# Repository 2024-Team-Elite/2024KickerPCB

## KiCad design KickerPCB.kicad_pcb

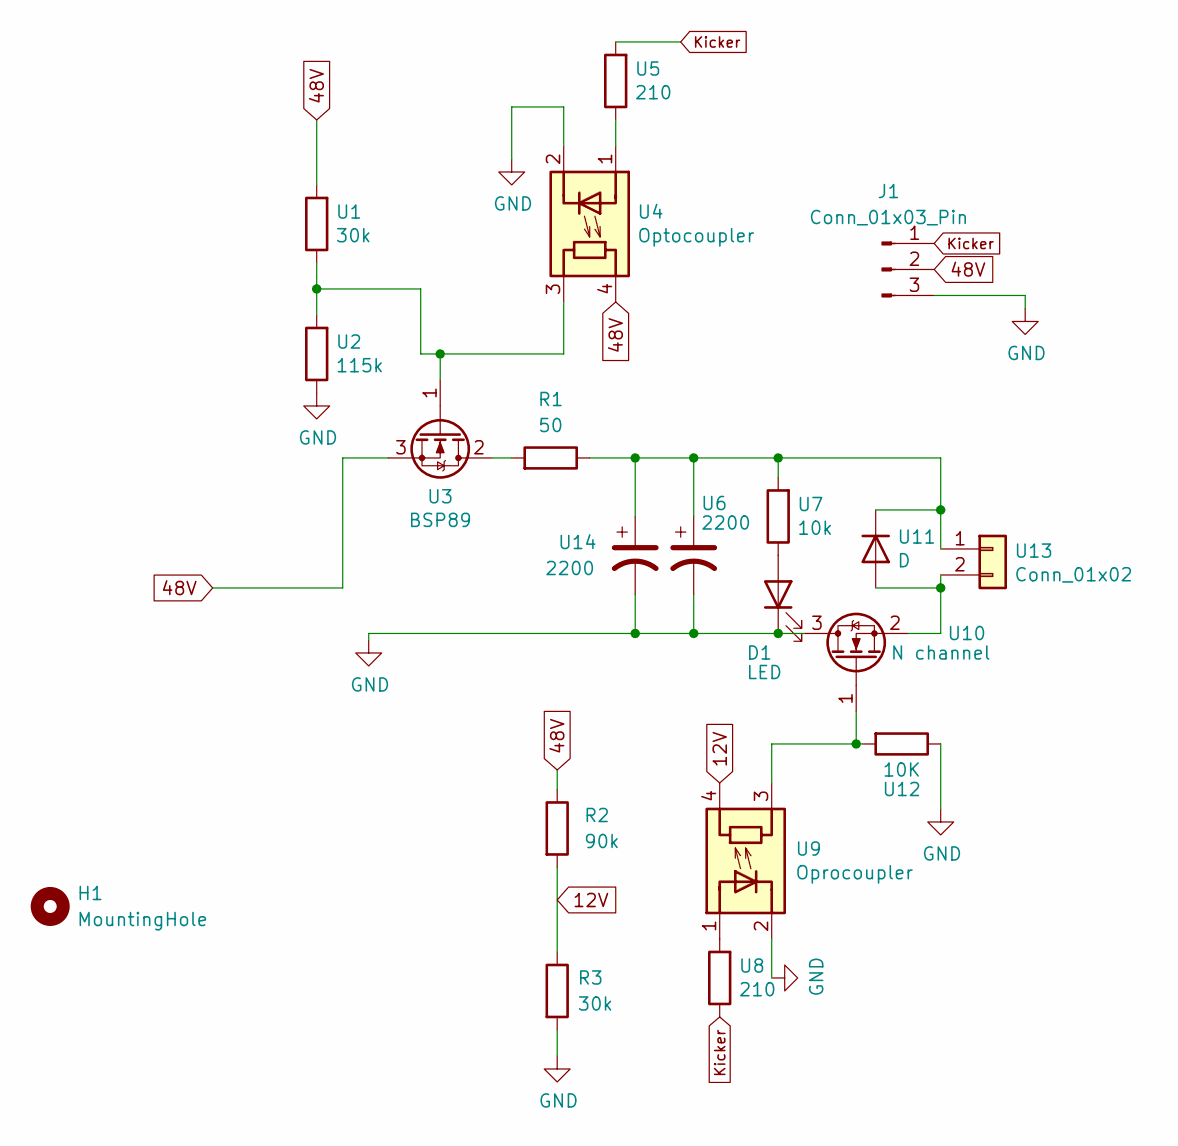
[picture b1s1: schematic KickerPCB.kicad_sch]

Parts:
D1: LED; LED_0805_2012Metric_Pad1.15x1.40mm_HandSolder
H1: MountingHole; MountingHole_3.2mm_M3_DIN965_Pad
J1: Conn_01x03_Pin; PinHeader_1x03_P2.54mm_Vertical
R1: 50; TO-220-2_Vertical
R2: 90k; R_0805_2012Metric_Pad1.20x1.40mm_HandSolder
R3: 30k; R_0805_2012Metric_Pad1.20x1.40mm_HandSolder
U1: 30k; R_0805_2012Metric_Pad1.20x1.40mm_HandSolder
U2: 115k; R_0805_2012Metric_Pad1.20x1.40mm_HandSolder
U3: BSP89; TO-220-3_Vertical
U4: Optocoupler; DIP-4_W7.62mm
U5, U8: 210; R_0805_2012Metric_Pad1.20x1.40mm_HandSolder
U6, U14: 2200; CP_Radial_D18.0mm_P7.50mm
U7: 10k; R_0805_2012Metric_Pad1.20x1.40mm_HandSolder
U9: Oprocoupler; DIP-4_W7.62mm
U10: N channel; TO-220-3_Vertical
U11: D; D_5W_P12.70mm_Horizontal
U12: 10K; R_0805_2012Metric_Pad1.20x1.40mm_HandSolder
U13: Conn_01x02; Pads_1x02

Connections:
12V: R2.2, R3.1, U9.4 (R)
48V: J1.2, R2.1, U1.2, U3.3 (S), U4.4 (R)
GND: D1.1 (K), J1.3, R3.2, U2.1, U4.2 (K), U6.2, U9.2 (K), U10.3 (D), U12.1, U14.2
Kicker: J1.1, U5.2, U8.1
unnamed: D1.2 (A), U7.1
unnamed: R1.2, U3.2 (D)
unnamed: U1.1, U2.2, U3.1 (G), U4.3 (R)
unnamed: U4.1 (A), U5.1
unnamed: U8.2, U9.1 (A)
unnamed: U9.3 (R), U10.1 (G), U12.2
unnamed: U10.2 (S), U11.2 (A), U13.2
unnamed: R1.1, U6.1, U7.2, U11.1 (K), U13.1, U14.1

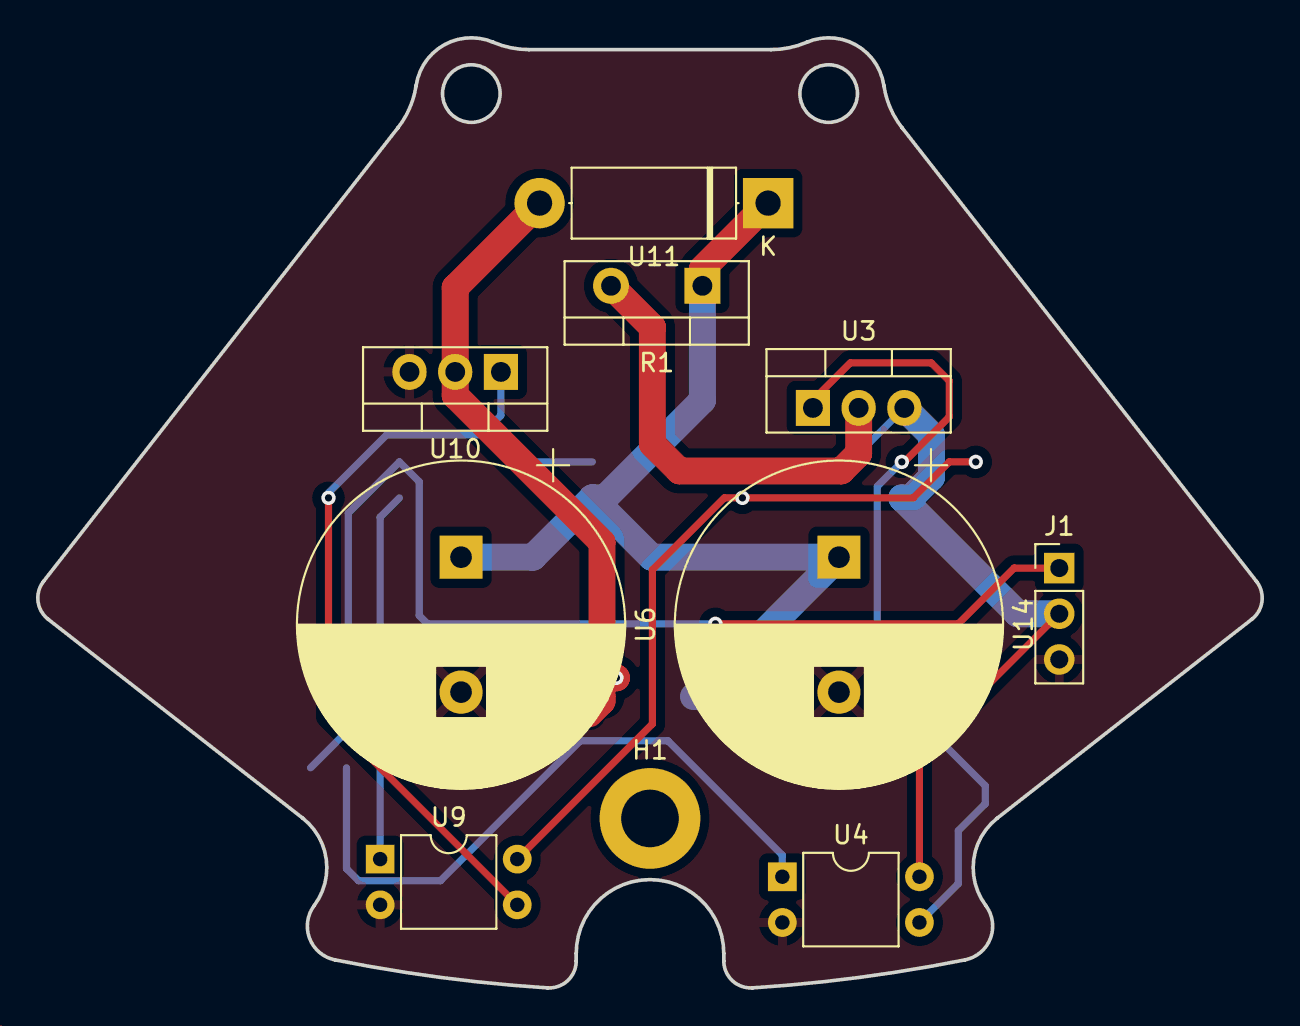
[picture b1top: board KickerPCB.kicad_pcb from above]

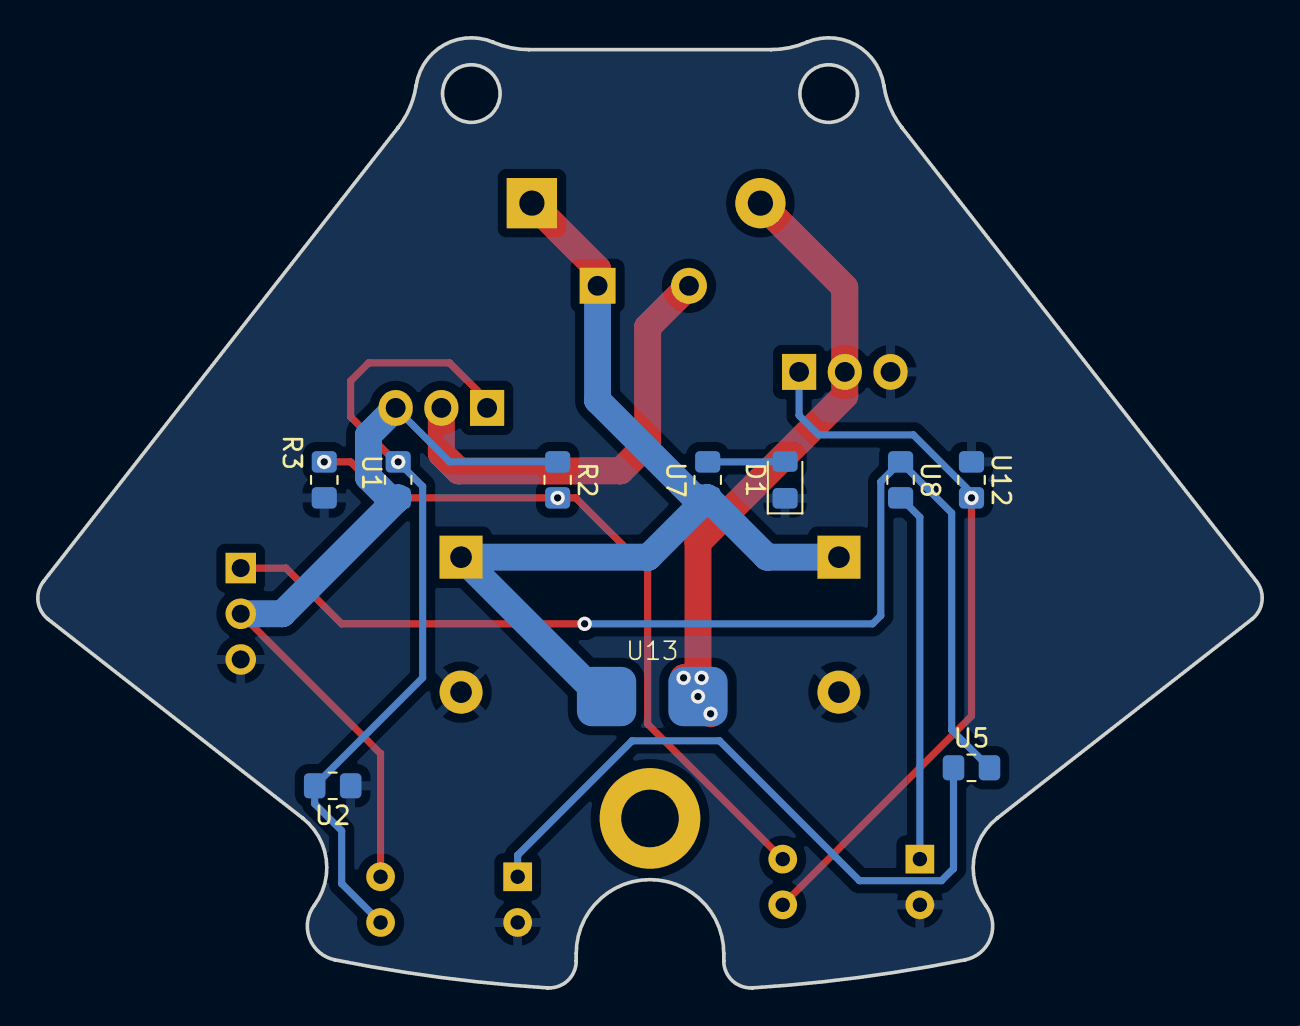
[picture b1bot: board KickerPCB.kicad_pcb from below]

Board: 2 copper layers, 68.0 x 52.8 mm, 20 parts (10 on the bottom side), 12 nets.

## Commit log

2024-02-25 Finished Kicker PCB
2024-02-25 idk why these files changed 💀
2024-03-03 Finished
2024-03-13 Moved parts for edges
2024-04-14 Cleaning
2024-04-21 Moved Caps
2024-04-21 Created Step file
